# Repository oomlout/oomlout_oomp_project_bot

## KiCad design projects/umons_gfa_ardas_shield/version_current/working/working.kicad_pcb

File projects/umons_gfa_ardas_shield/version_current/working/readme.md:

# OOMP Project  
## ardas-shield  by UMONS-GFA  
  
oomp key: oomp_projects_flat_umons_gfa_ardas_shield  
(snippet of original readme)  

  full source readme at [readme_src.md](readme_src.md)  
  
source repo at: [https://github.com/UMONS-GFA/ardas-shield](https://github.com/UMONS-GFA/ardas-shield)  
## Board  

## Schematic  

[schematic pdf](working_schematic.pdf)  
## Images

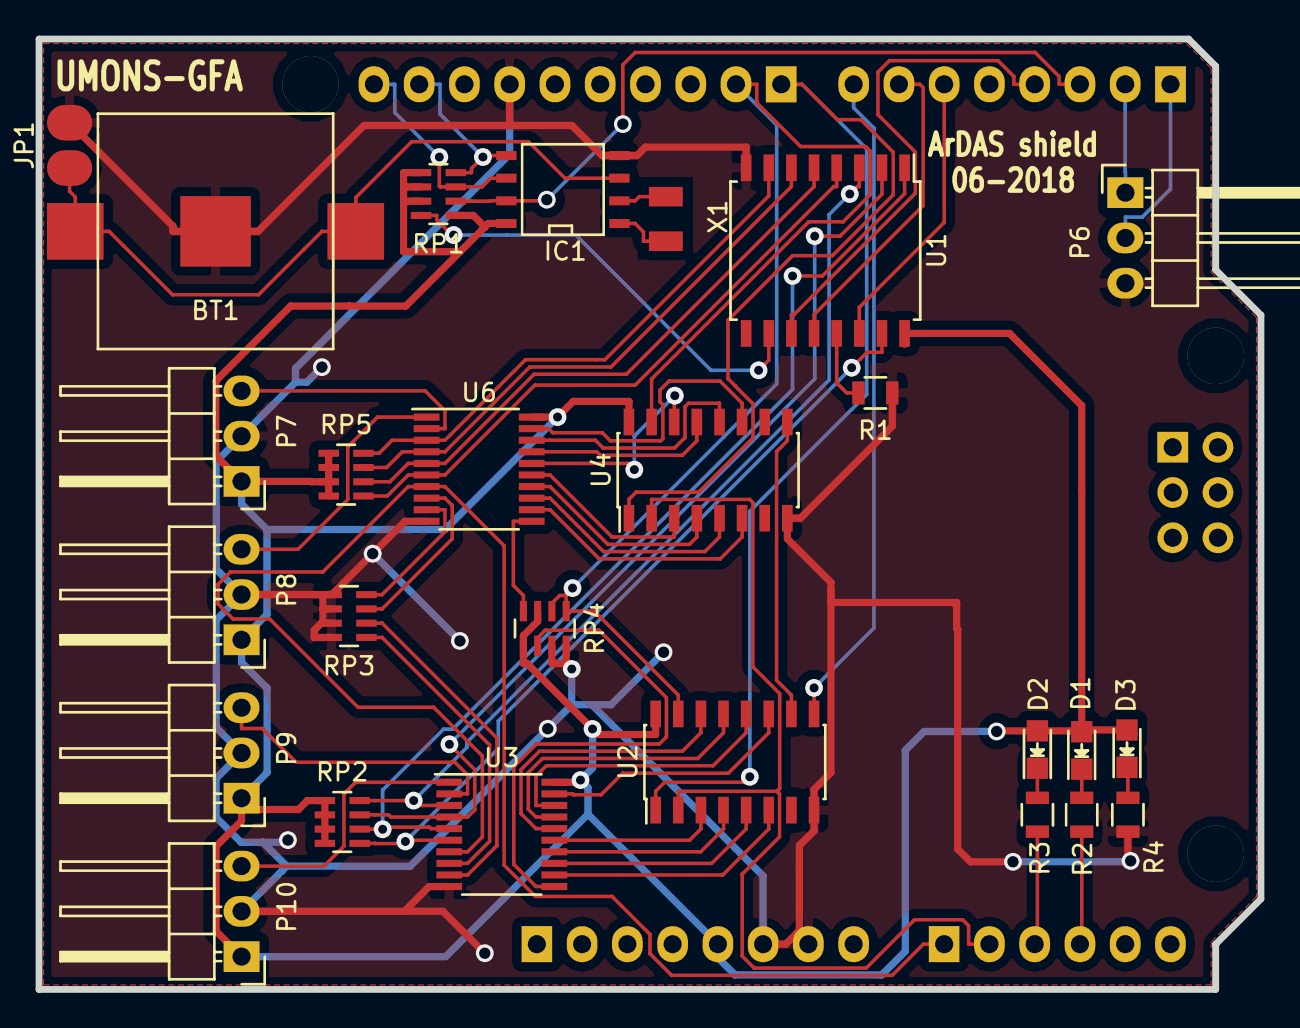
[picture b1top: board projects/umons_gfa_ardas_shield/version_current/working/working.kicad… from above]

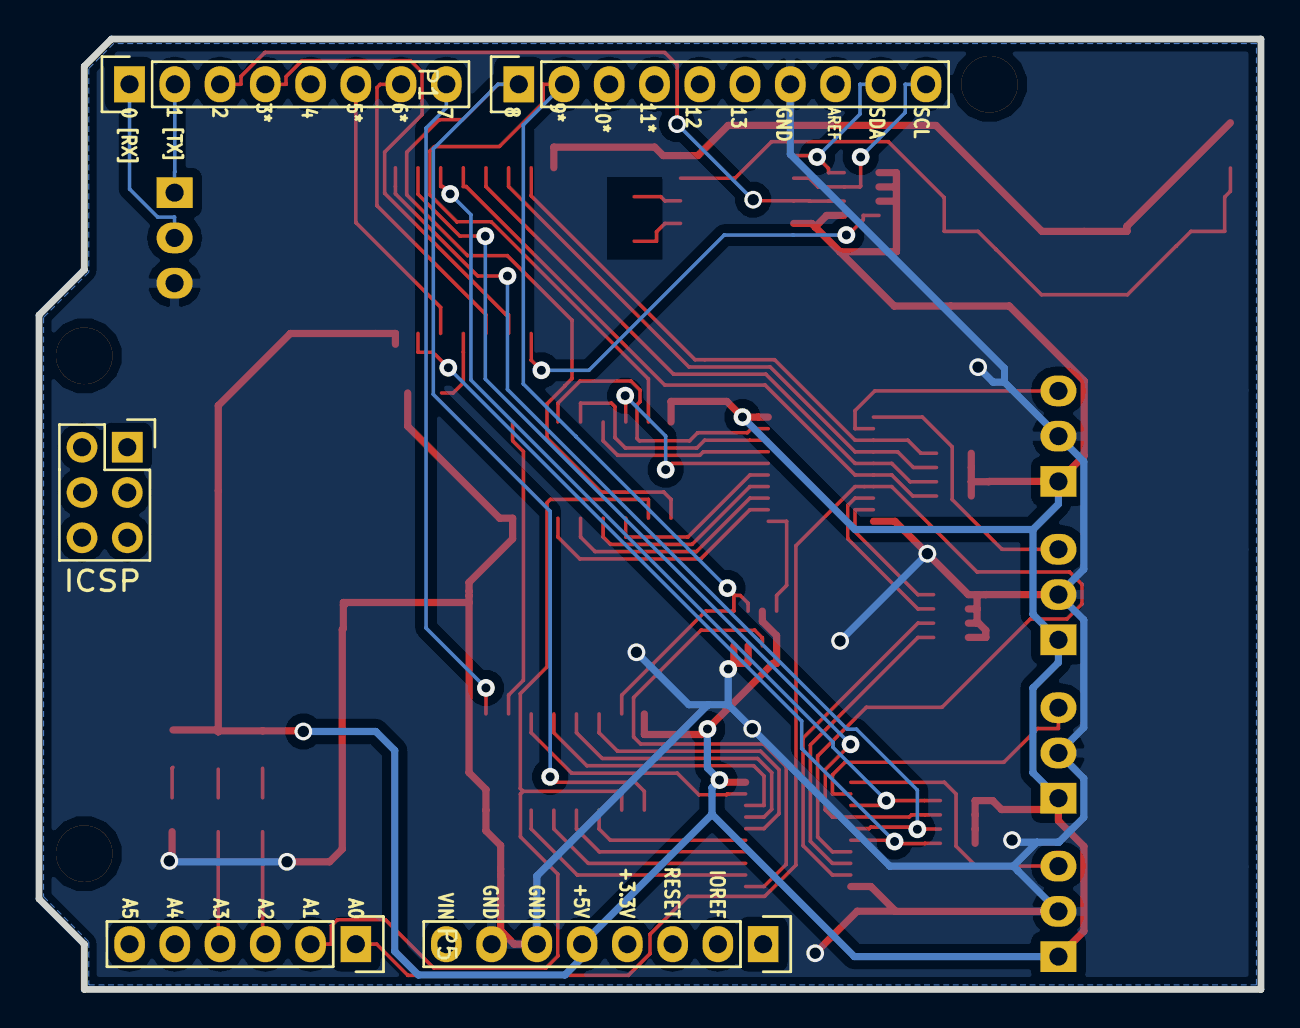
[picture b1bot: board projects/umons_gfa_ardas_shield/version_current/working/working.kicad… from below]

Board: 2 copper layers, 68.6 x 53.3 mm, 34 parts (5 on the bottom side), 60 nets.

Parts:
BT1: Battery; BATTERY_KEYSTONE_12mm
D1: LED; LED-0805
D2: LED Yellow; LED-0805
D3: LED Red; LED-0805
IC1: DS1307; SOIC-8-N
JP1: Jumper_NO_Small; small_no_jumper
P1: CONN_10; Pin_Header_Straight_1x10
P2, P3: CONN_8; Pin_Header_Straight_1x08
P4: CONN_ICSP; Socket_Strip_Straight_2x03
P5: CONN_6; Pin_Header_Straight_1x06
P6: TTL_COMM; Pin_Header_Angled_1x03
P7, P8, P9, P10: CONN_01X03; Pin_Header_Angled_1x03
R1: 10k; R_0805
R2, R3: 150 Ohm; R_0805
R4: 160 Ohm; R_0805
RP1: R_4x4.7k; R_Array_Convex_4x0603
RP2, RP3, RP4, RP5: R_4x10k; R_Array_Convex_4x0603
U1: 74HC595; SOIC-16_7.5x10.3mm_Pitch1.27mm
U2, U4: 74HC165; SOIC-16_3.9x9.9mm_Pitch1.27mm
U3, U6: SN74LV8154; TSSOP-20_4.4x6.5mm_Pitch0.65mm
V4, V5, V6: MountingHole_125mil
X1: CRYSTAL; XTAL_ABRACON_ABS07

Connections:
+5V: D1.2, D2.2, D3.2, IC1.8, P2.5, P7.1, P8.1, P9.1, P10.1, RP1.1, RP1.5, RP1.6, RP1.7, RP2.1, RP2.2, RP2.3, RP2.4, RP4.3, RP4.5, RP5.1, RP5.2, RP5.3, RP5.4, U1.16, U2.16, U3.20, U4.16, U6.20
A04: IC1.5, P1.9, RP1.4
A05: IC1.6, P1.10, RP1.3
CH1: P10.3, U3.1
CH2: P9.3, U3.2
CH3: P8.3, U6.1
CH4: P7.3, U6.2
D00: P3.1, P6.2
D01: P3.2, P6.1
D02: IC1.7, P3.3, RP1.2
D03: P3.4, U1.11
D05: P3.6, U1.14
D06: P3.7, U1.12
D07: P3.8, U2.9
D08: P1.1, U2.1, U4.1
D09: P1.2, RP4.1, RP4.2, U2.15, U4.15
D14: P5.1, U3.7, U6.7
D15: P5.2, U2.2, U4.2
D16: P5.3, R3.2
D17: P5.4, R2.2
GND: BT1.2, IC1.4, JP1.1, P1.7, P2.6, P2.7, P6.3, P7.2, P8.2, P9.2, P10.2, R1.1, R4.2, RP3.5, RP3.6, RP3.7, RP3.8, RP4.7, RP4.8, U1.8, U2.8, U3.10, U4.8, U6.10
unnamed: BT1.1, IC1.3, JP1.2
unnamed: D1.1, R2.1
unnamed: D2.1, R3.1
unnamed: D3.1, R4.1
unnamed: IC1.1, X1.1
unnamed: IC1.2, X1.2
unnamed: R1.2, U1.13
unnamed: RP1.8, U1.10
unnamed: RP2.5, U1.15, U3.6
unnamed: RP2.6, U1.1, U3.5
unnamed: RP2.7, U1.2, U3.4
unnamed: RP2.8, U1.3, U3.3
unnamed: RP3.1, U3.8
unnamed: RP3.2, U3.9
unnamed: RP3.3, U6.8
unnamed: RP3.4, U6.9
unnamed: RP4.4, U6.11
unnamed: RP4.6, U3.11
unnamed: RP5.5, U1.4, U6.6
unnamed: RP5.6, U1.5, U6.5
unnamed: RP5.7, U1.6, U6.4
unnamed: RP5.8, U1.7, U6.3
unnamed: U2.3, U3.15
unnamed: U2.4, U3.14
unnamed: U2.5, U3.13
unnamed: U2.6, U3.12
unnamed: U2.10, U4.9
unnamed: U2.11, U3.19
unnamed: U2.12, U3.18
unnamed: U2.13, U3.17
unnamed: U2.14, U3.16
unnamed: U4.3, U6.15
unnamed: U4.4, U6.14
unnamed: U4.5, U6.13
unnamed: U4.6, U6.12
unnamed: U4.11, U6.19
unnamed: U4.12, U6.18
unnamed: U4.13, U6.17
unnamed: U4.14, U6.16

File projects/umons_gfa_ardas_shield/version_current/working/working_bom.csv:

"Id";"Designator";"Footprint";"Quantity";"Designation";"Supplier and ref";
1;"V6,V4,V5";"MountingHole_125mil";3;"";;;
2;"BT1";"BATTERY_KEYSTONE_12mm";1;"Battery";;;
3;"IC1";"SOIC-8-N";1;"DS1307";;;
4;"JP1";"small_no_jumper";1;"Jumper_NO_Small";;;
5;"P1";"Pin_Header_Straight_1x10";1;"CONN_10";;;
6;"P2,P3";"Pin_Header_Straight_1x08";2;"CONN_8";;;
7;"P4";"Socket_Strip_Straight_2x03";1;"CONN_ICSP";;;
8;"P5";"Pin_Header_Straight_1x06";1;"CONN_6";;;
9;"P6";"Pin_Header_Angled_1x03";1;"TTL_COMM";;;
10;"P7,P8,P9,P10";"Pin_Header_Angled_1x03";4;"CONN_01X03";;;
11;"R1";"R_0805";1;"10k";;;
12;"R2,R3";"R_0805";2;"150 Ohm";;;
13;"R4";"R_0805";1;"160 Ohm";;;
14;"U1";"SOIC-16_7.5x10.3mm_Pitch1.27mm";1;"74HC595";;;
15;"U2,U4";"SOIC-16_3.9x9.9mm_Pitch1.27mm";2;"74HC165";;;
16;"X1";"XTAL_ABRACON_ABS07";1;"CRYSTAL";;;
17;"U6,U3";"TSSOP-20_4.4x6.5mm_Pitch0.65mm";2;"SN74LV8154";;;
18;"RP1";"R_Array_Convex_4x0603";1;"R_4x4.7k";;;
19;"RP2,RP3,RP4,RP5";"R_Array_Convex_4x0603";4;"R_4x10k";;;
20;"D2";"LED-0805";1;"LED Yellow";;;
21;"D3";"LED-0805";1;"LED Red";;;
22;"D1";"LED-0805";1;"LED Green";;;

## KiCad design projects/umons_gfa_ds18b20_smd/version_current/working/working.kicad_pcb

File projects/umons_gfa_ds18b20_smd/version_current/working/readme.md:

# OOMP Project  
## ds18b20-smd  by UMONS-GFA  
  
oomp key: oomp_projects_flat_umons_gfa_ds18b20_smd  
(snippet of original readme)  

  full source readme at [readme_src.md](readme_src.md)  
  
source repo at: [https://github.com/UMONS-GFA/ds18b20-smd](https://github.com/UMONS-GFA/ds18b20-smd)  
## Board  

## Schematic  

[schematic pdf](working_schematic.pdf)  
## Images

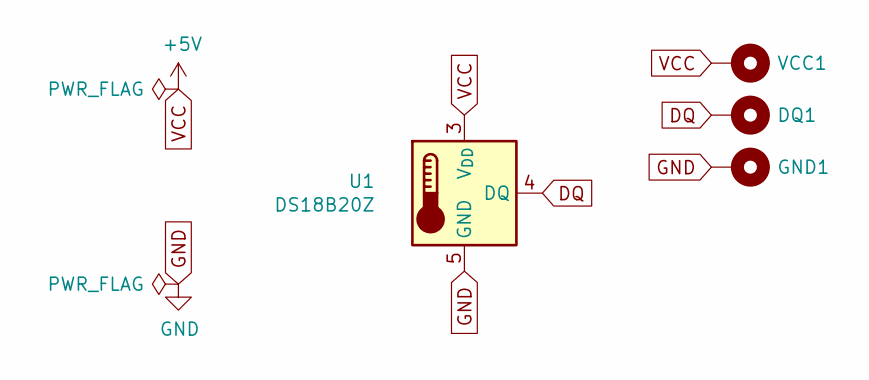
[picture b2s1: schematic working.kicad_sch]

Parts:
DQ1: Pad; PAD3mmx5mm
GND1: Pad; PAD3mmx5mm
U1: DS18B20Z; SOIC-8-N
VCC1: Pad; PAD3mmx5mm

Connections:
DQ: DQ1.1, U1.4 (DQ)
GND: GND1.1, U1.5 (GND)
VCC: U1.3 (V_{DD}), VCC1.1

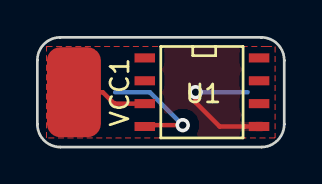
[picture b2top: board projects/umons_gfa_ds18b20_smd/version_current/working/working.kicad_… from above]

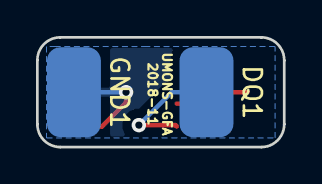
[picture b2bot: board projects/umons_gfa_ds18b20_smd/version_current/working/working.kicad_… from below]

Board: 2 copper layers, 13.7 x 6.1 mm, 4 parts (2 on the bottom side), 3 nets.

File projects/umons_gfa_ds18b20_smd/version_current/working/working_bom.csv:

"Id";"Designator";"Footprint";"Quantity";"Designation";"Supplier and ref";
1;"U1";"SOIC-8-N";1;"DS18B20Z";;;
2;"DQ1,GND1,VCC1";"PAD3mmx5mm";3;"Pad";;;

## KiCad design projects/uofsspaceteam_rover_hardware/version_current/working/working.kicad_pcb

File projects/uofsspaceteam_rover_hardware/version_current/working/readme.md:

# rover-hardware by UofSSpaceTeam  
This is a harvested standardized copy of a project from github.  
The original project can be found at:  
https://github.com/UofSSpaceTeam/rover-hardware  
Please consult that link for additional, details, files, and license information.  
Note: It was auto harvested and if the original repo had more than one board file or anything out of the ordinary the files here are likely not representative.

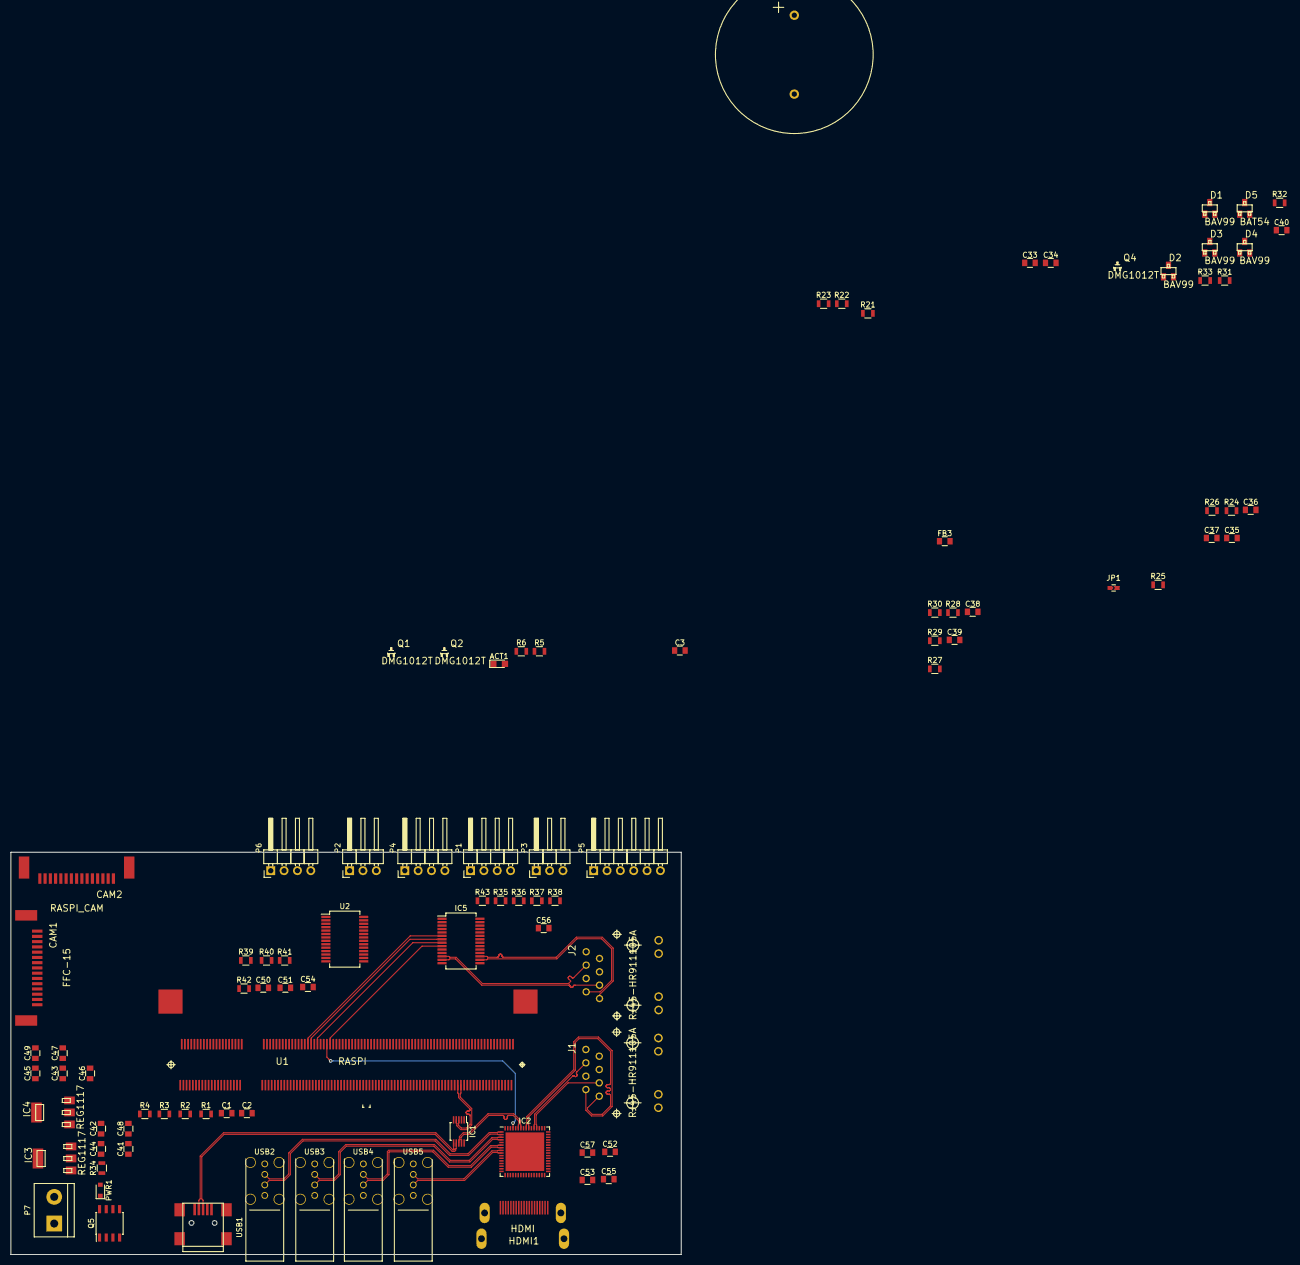
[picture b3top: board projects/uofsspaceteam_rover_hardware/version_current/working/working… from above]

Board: 4 copper layers, 127.5 x 76.5 mm, 141 parts (0 on the bottom side), 114 nets.

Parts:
ACT1: LED_0805
C1, C3, C21, C22, C26, C27, C30, C34, C41, C42, C45, C46, C47, C48, C49, C50: 10u; C_0805
C2, C5, C6, C7, C8: 20p; C_0805
C4, C9, C10, C11, C12, C13, C14, C15, C16, C17, C18, C19, C23, C24, C25, C28, C29, C31, C32, C33, C38, C39, C40, C53, C54, C55, C56, C57: 100n; C_0805
C20: 1u; C_0805
C35, C36, C37: 0.1u; C_0805
C43, C44: C_0805
C51, C52: 0.01u; C_0805
CAM1: FFC-15; FFC-15-PICAM
CAM2: RASPI_CAM; FFC-15-PICAM
D1, D2, D3, D4: BAV99; DIODE_SOT23
D5: BAT54; DIODE_SOT23
FB1, FB2: FERRITE_BEAD; C_0805
FB3: 80mA Ferrite; C_0805
HDMI1: HDMI; RASPI_HDMI
IC1: FSUSB42MSOP10; MSOP-10_3x3mm_Pitch0.5mm
IC2: RASPI_LAN9514; QFN-64-1EP_9x9mm_Pitch0.5mm
IC3, IC4: REG1117; BURR-BROWN_SOT223
IC5: ENC28J60; SSOP-28_5.3x10.2mm_Pitch0.65mm
J1, J2: RJ45-HR911105A; HANRUN_RJ45
JP1: Jumper_NC_Small; J_0603
P1: CONN_I2C; Pin_Header_Angled_1x04_Pitch2.54mm
P2: SERVO_PWM0; Pin_Header_Angled_1x03_Pitch2.54mm
P3: SERVO_PWM1; Pin_Header_Angled_1x03_Pitch2.54mm
P4: CONN_UART0; Pin_Header_Angled_1x04_Pitch2.54mm
P5: CONN_UART1_3DR; Pin_Header_Angled_1x06_Pitch2.54mm
P6: CAN_CONN_01X04; Pin_Header_Angled_1x04_Pitch2.54mm
P7: 5V POWER CONN; bornier2
PWR1: D_0805
Q1, Q2, Q3, Q4: DMG1012T; TRANSISTOR-FET_SC75_INFINEON
Q5: FDS6681Z; SOIC-8_3.9x4.9mm_Pitch1.27mm
R1, R2, R3, R26, R33: 100k; R_0805
R4, R5, R9, R10: 47k; R_0805
R6, R22, R23, R27, R28, R29, R30, R31, R32, R34: 1k8; R_0805
R7, R8, R25, R42, R43: 1k; R_0805
R11: 10; R_0805
R12, R13, R14, R15: 49.9; R_0805
R16: 12k4; R_0805
R17, R18, R19, R20: 12k; R_0805
R21: 400; R_0805
R24: 100; R_0805
R35, R36: 10k; R_0805
R37, R38, R40, R41: 50; R_0805
R39: 2.32k; R_0805
SP1: SPEAKER; AI-3035-TWT
U1: RASPI; RASPI_SO-DIMM
U2: MCP25625; SSOP-28_5.3x10.2mm_Pitch0.65mm
USB1: USB-TYPA; MINI-B-USBR
USB2, USB3, USB4, USB5: USB2; USB-A-UPRIGHT

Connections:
+1V8: C43.1, C45.1, C47.1, IC3.2, R5.1, R33.1, U1.183, U1.184, U1.185, U1.186
+3V3: C1.1, C3.1, C4.1, C10.1, C12.1, C23.1, C24.1, C25.1, C31.2, C32.2, C33.2, C35.1, C37.1, C38.2, C39.2, C44.1, C46.1, C48.1, C49.1, C53.1, C54.1, C55.1, C56.1, C57.1, CAM1.15, CAM2.15, FB2.2, FB3.1, IC1.1, IC2.11, IC2.19, IC2.27, IC2.33, IC2.39, IC2.40, IC2.46, IC4.2, IC5.15, IC5.19, IC5.20, IC5.25, IC5.28, P1.1, P4.1, R6.1, R7.1, R8.1, R9.1, R11.2, R12.1, R13.2, R14.2, R15.2, R18.1, R19.2, R20.1, R22.1, R23.2, R26.1, R27.1, R28.1, R29.1, R30.1, R34.1, R35.1, R36.1, U1.39, U1.40, U1.41, U1.42, U1.189, U1.190, U1.191, U1.192, U1.193, U1.194, U2.1, U2.19
+5V: C21.1, C22.1, C26.1, C27.1, C34.2, C36.1, C41.1, C42.1, D5.2, IC3.3, IC4.3, P2.2, P3.2, P5.3, P6.1, Q5.1, Q5.2, Q5.3, R31.1, R32.1, U1.197, U1.198, U1.199, U1.200, U2.27, USB2.VBUS, USB3.VBUS, USB4.VBUS, USB5.VBUS
/CAM0_C_N: CAM1.8, U1.144
/CAM0_C_P: CAM1.9, U1.142
/CAM0_D0_N: CAM1.2, U1.138
/CAM0_D0_P: CAM1.3, U1.136
/CAM0_D1_N: CAM1.5, U1.150
/CAM0_D1_P: CAM1.6, U1.148
/CAM1_C_N: CAM2.8, U1.149
/CAM1_C_P: CAM2.9, U1.147
/CAM1_D0_N: CAM2.2, U1.161
/CAM1_D0_P: CAM2.3, U1.159
/CAM1_D1_N: CAM2.5, U1.155
/CAM1_D1_P: CAM2.6, U1.153
/GPIO0: CAM2.14, R28.2, U1.3
/GPIO1: CAM2.13, R30.2, U1.5
/GPIO5: CAM2.12, U1.17
/GPIO6: IC2.12, R19.1, U1.21
/GPIO8: U1.27, U2.17
/GPIO9: U1.29, U2.16
/GPIO10: U1.33, U2.15
/GPIO11: U1.35, U2.14
/GPIO21: CAM2.11, U1.71
/GPIO25: U1.83, U2.13
/GPIO28: CAM1.14, R3.2, R27.2, U1.28
/GPIO29: CAM1.13, R1.2, R29.2, U1.30
/GPIO30: CAM1.11, U1.34
/GPIO31: CAM1.12, U1.36
/GPIO34: IC5.23, U1.52
/GPIO39: IC5.4, U1.66
/GPIO40: IC5.6, U1.70
/GPIO41: IC5.7, U1.72
/GPIO42: IC5.8, U1.76
/GPIO43: U1.78, U2.9
/GPIO44: IC2.61, R2.2, U1.82
/GPIO45: IC5.9, R35.2, U1.84
/HDMI_CEC: C2.1, D1.3, HDMI1.13, U1.171
/HDMI_CK_N: HDMI1.12, U1.111
/HDMI_CK_P: HDMI1.10, U1.113
/HDMI_D0_N: HDMI1.9, U1.117
/HDMI_D0_P: HDMI1.7, U1.119
/HDMI_D1_N: HDMI1.6, U1.123
/HDMI_D1_P: HDMI1.4, U1.125
/HDMI_D2_N: HDMI1.3, U1.129
/HDMI_D2_P: HDMI1.1, U1.131
/HDMI_SCL: D2.3, HDMI1.15, R32.2, U1.175
/HDMI_SDA: D3.3, HDMI1.16, R31.2, U1.173
/USBD_N: IC1.4, U1.167
/USBD_P: IC1.3, U1.165
/USSTCM CONN/SCL: P1.4, R23.1
/USSTCM CONN/SDA: P1.3, R22.2
/USSTCM LAN/ETH_RX_N: C8.1, IC2.53, J1.6, R12.2
/USSTCM LAN/ETH_RX_P: C7.1, IC2.52, J1.3, R13.1
/USSTCM LAN/ETH_TX_N: C6.1, IC2.56, J1.2, R14.1
/USSTCM LAN/ETH_TX_P: C5.1, IC2.55, J1.1, R15.1
/USSTCM LAN/NLNKA_LED: IC2.21, J1.10
/USSTCM LAN/NSPD_LED: IC2.22, J1.11
/USSTCM LAN/RCT: C9.1, J1.4, J1.5, R11.1
/USSTCM LAN/USB2_N: IC2.1, USB2.D-
/USSTCM LAN/USB2_P: IC2.2, USB2.D+
/USSTCM LAN/USB3_N: IC2.3, USB3.D-
/USSTCM LAN/USB3_P: IC2.4, USB3.D+
/USSTCM LAN/USB4_N: IC2.6, USB4.D-
/USSTCM LAN/USB4_P: IC2.7, USB4.D+
/USSTCM LAN/USB5_N: IC2.8, USB5.D-
/USSTCM LAN/USB5_P: IC2.9, USB5.D+
/USSTCM LAN/USB_BOOT_N: IC1.6, USB1.D-
/USSTCM LAN/USB_BOOT_P: IC1.7, USB1.D+
/USSTCM LAN/USB_LAN_N: IC1.8, IC2.58
/USSTCM LAN/USB_LAN_P: IC1.9, IC2.59
/USSTCM LAN/VDD18CORE: C28.2, C29.2, C30.2, IC2.15, IC2.38
/USSTCM LAN/VDD18PLL: C15.2, FB1.1, IC2.48
/USSTCM_CAN_LITE/CAN_N: P6.3, R24.2, U2.4
/USSTCM_CAN_LITE/CAN_P: JP1.2, P6.4, U2.3
/USSTCM_LAN2/LNKA_LED: IC5.27, J2.9
/USSTCM_LAN2/RCT: C51.1, J2.5, R37.2, R38.1
/USSTCM_LAN2/RD+: IC5.13, J2.3, R37.1
/USSTCM_LAN2/RD-: IC5.12, J2.6, R38.2
/USSTCM_LAN2/SPD_LED: IC5.26, J2.12
/USSTCM_LAN2/TCT: C52.1, FB3.2, J2.4, R40.2, R41.1
/USSTCM_LAN2/TD+: IC5.17, J2.1, R40.1
/USSTCM_LAN2/TD-: IC5.16, J2.2, R41.2
/USSTCM_VIDEO/5V_HDMI: C40.1, D1.2, D2.2, D3.2, D4.2, D5.1, HDMI1.18
/USSTCM_VIDEO/GPIO46: Q4.3, R33.2
/VUSB_BOOT: Q1.1, Q3.1, R4.1, R10.1, USB1.VBUS
GND: C1.2, C2.2, C3.2, C4.2, C5.2, C6.2, C7.2, C8.2, C9.2, C10.2, C11.1, C12.2, C13.1, C14.1, C15.1, C16.1, C17.1, C18.1, C19.1, C20.1, C21.2, C22.2, C23.2, C24.2, C25.2, C26.2, C27.2, C28.1, C29.1, C30.1, C31.1, C32.1, C33.1, C34.1, C35.2, C36.2, C37.2, C38.1, C39.1, C40.2, C41.2, C42.2, C43.2, C44.2, C45.2, C46.2, C47.2, C48.2, C49.2, C50.2, C51.2, C52.2, C53.2, C54.2, C55.2, C56.2, C57.2, CAM1.1, CAM1.4, CAM1.7, CAM1.10, CAM1.16, CAM1.17, CAM2.1, CAM2.4, CAM2.7, CAM2.10, CAM2.16, CAM2.17, D1.1, D2.1, D3.1, D4.1, HDMI1.2, HDMI1.5, HDMI1.8, HDMI1.11, HDMI1.17, HDMI1.P$1, HDMI1.P$2, HDMI1.P$3, HDMI1.P$4, IC1.5, IC1.10, IC2.34, IC2.44, IC2.65, IC3.1, IC4.1, IC5.2, IC5.11, IC5.18, IC5.21, IC5.22, J1.8, J2.8, P1.2, P2.1, P3.1, P4.2, P5.1, P6.2, P7.2, PWR1.1, Q2.2, Q3.2, Q4.2, Q5.4, R1.1, R2.1, R3.1, R4.2, R10.2, R16.1, R17.2, R25.2, R39.2, R42.1, R43.1, SP1.2, U1.1, U1.7, U1.13, U1.19, U1.25, U1.26, U1.31, U1.32, U1.37, U1.38, U1.43, U1.44, U1.49, U1.50, U1.55, U1.56, U1.61, U1.62, U1.67, U1.68, U1.73, U1.74, U1.79, U1.80, U1.85, U1.86, U1.91, U1.92, U1.97, U1.98, U1.103, U1.104, U1.109, U1.110, U1.115, U1.116, U1.121, U1.122, U1.127, U1.133, U1.134, U1.139, U1.140, U1.145, U1.146, U1.151, U1.152, U1.157, U1.163, U1.164, U1.168, U1.169, U1.170, U1.181, U1.182, U1.187, U1.188, U1.195, U1.196, U1.G1, U1.G2, U2.26, USB1.GND, USB2.GND, USB3.GND, USB4.GND, USB5.GND
unnamed: ACT1.1, Q1.2, Q2.3
unnamed: ACT1.2, R6.2
unnamed: C11.2, C14.2, C16.2, C17.2, C18.2, C19.2, FB2.1, IC2.5, IC2.10, IC2.49, IC2.51, IC2.54, IC2.57, IC2.64
unnamed: C20.2, FB1.2, IC2.62
unnamed: C50.1, IC5.1
unnamed: D4.3, HDMI1.19, Q4.1
unnamed: IC1.2, Q3.3, R9.2
unnamed: IC2.28, R20.2
unnamed: IC2.41, R18.2
unnamed: IC2.50, R16.2
unnamed: IC2.63, R17.1
unnamed: IC5.10, R36.2
unnamed: IC5.14, R39.1
unnamed: J1.9, R8.2
unnamed: J1.12, R7.2
unnamed: J2.10, R43.2
unnamed: J2.11, R42.2
unnamed: JP1.1, R24.1
unnamed: P7.1, Q5.5, Q5.6, Q5.7, Q5.8
unnamed: PWR1.2, R34.2
unnamed: Q1.3, U1.2
unnamed: Q2.1, R5.2, U1.90
unnamed: R21.1, SP1.1
unnamed: R25.1, U2.5
unnamed: R26.2, U2.18
unnamed: U2.20, U2.24
unnamed: U2.21, U2.28

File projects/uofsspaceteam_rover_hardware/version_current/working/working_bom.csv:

"Id";"Designator";"Footprint";"Quantity";"Designation";"Supplier and ref";
1;"C1,C3,C21,C22,C26,C27,C30,C34,C41,C42,C45,C46,C47,C48,C49,C50";"C_0805";16;"10u";;;
2;"C2,C5,C6,C7,C8";"C_0805";5;"20p";;;
3;"C4,C9,C10,C11,C12,C13,C14,C15,C16,C17,C18,C19,C23,C24,C25,C28,C29,C31,C32,C33,C38,C39,C40,C53,C54,C55,C56,C57";"C_0805";28;"100n";;;
4;"C20";"C_0805";1;"1u";;;
5;"C35,C36,C37";"C_0805";3;"0.1u";;;
6;"C43,C44";"C_0805";2;"~";;;
7;"C51,C52";"C_0805";2;"0.01u";;;
8;"D1,D2,D3,D4";"DIODE_SOT23";4;"BAV99";;;
9;"D5";"DIODE_SOT23";1;"BAT54";;;
10;"FB1,FB2";"C_0805";2;"FERRITE_BEAD";;;
11;"HDMI1";"RASPI_HDMI";1;"HDMI";;;
12;"IC3,IC4";"BURR-BROWN_SOT223";2;"REG1117";;;
13;"IC5";"SSOP-28_5.3x10.2mm_Pitch0.65mm";1;"ENC28J60";;;
14;"JP1";"J_0603";1;"Jumper_NC_Small";;;
15;"P1";"Pin_Header_Angled_1x04_Pitch2.54mm";1;"CONN_I2C";;;
16;"P2";"Pin_Header_Angled_1x03_Pitch2.54mm";1;"SERVO_PWM0";;;
17;"P3";"Pin_Header_Angled_1x03_Pitch2.54mm";1;"SERVO_PWM1";;;
18;"P4";"Pin_Header_Angled_1x04_Pitch2.54mm";1;"CONN_UART0";;;
19;"P5";"Pin_Header_Angled_1x06_Pitch2.54mm";1;"CONN_UART1_3DR";;;
20;"P6";"Pin_Header_Angled_1x04_Pitch2.54mm";1;"CAN_CONN_01X04";;;
21;"P7";"bornier2";1;"5V POWER CONN";;;
22;"Q1,Q2,Q3,Q4";"TRANSISTOR-FET_SC75_INFINEON";4;"DMG1012T";;;
23;"Q5";"SOIC-8_3.9x4.9mm_Pitch1.27mm";1;"FDS6681Z";;;
24;"R1,R2,R3,R26,R33";"R_0805";5;"100k";;;
25;"R4,R5,R9,R10";"R_0805";4;"47k";;;
26;"R6,R22,R23,R27,R28,R29,R30,R31,R32,R34";"R_0805";10;"1k8";;;
27;"R7,R8,R25,R42,R43";"R_0805";5;"1k";;;
28;"R11";"R_0805";1;"10";;;
29;"R12,R13,R14,R15";"R_0805";4;"49.9";;;
30;"R16";"R_0805";1;"12k4";;;
31;"R17,R18,R19,R20";"R_0805";4;"12k";;;
32;"R21";"R_0805";1;"400";;;
33;"R24";"R_0805";1;"100";;;
34;"R35,R36";"R_0805";2;"10k";;;
35;"R37,R38,R40,R41";"R_0805";4;"50";;;
36;"R39";"R_0805";1;"2.32k";;;
37;"U1";"RASPI_SO-DIMM";1;"RASPI";;;
38;"U2";"SSOP-28_5.3x10.2mm_Pitch0.65mm";1;"MCP25625";;;
39;"CAM1";"FFC-15-PICAM";1;"FFC-15";;;
40;"CAM2";"FFC-15-PICAM";1;"RASPI_CAM";;;
41;"PWR1";"D_0805";1;"~";;;
42;"IC2";"QFN-64-1EP_9x9mm_Pitch0.5mm";1;"RASPI_LAN9514";;;
43;"USB2,USB3,USB4,USB5";"USB-A-UPRIGHT";4;"USB2";;;
44;"USB1";"MINI-B-USBR";1;"USB-TYPA";;;
45;"ACT1";"LED_0805";1;"~";;;
46;"IC1";"MSOP-10_3x3mm_Pitch0.5mm";1;"FSUSB42MSOP10";;;
47;"FB3";"C_0805";1;"80mA Ferrite";;;
48;"SP1";"AI-3035-TWT";1;"SPEAKER";;;

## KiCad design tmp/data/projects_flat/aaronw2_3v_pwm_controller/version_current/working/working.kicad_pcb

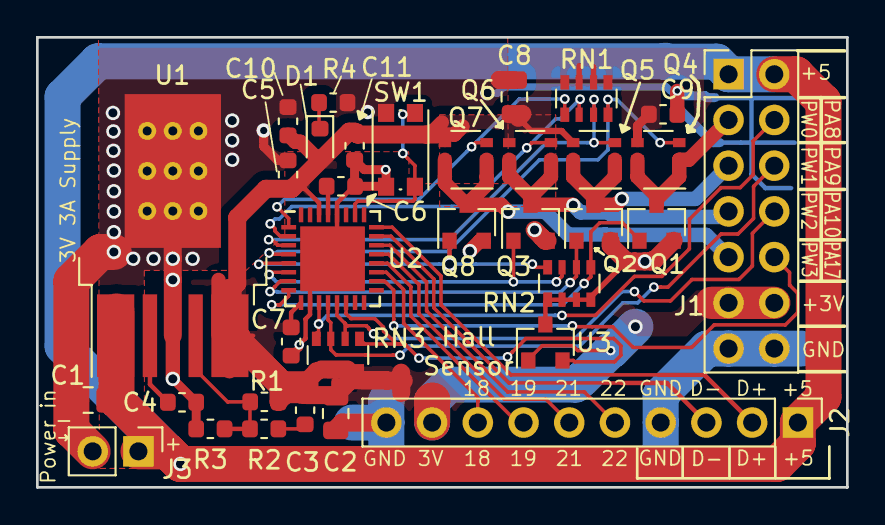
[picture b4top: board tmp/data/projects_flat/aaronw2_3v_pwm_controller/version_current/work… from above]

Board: 2 copper layers, 45.0 x 25.0 mm, 34 parts (0 on the bottom side), 32 nets.

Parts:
C1: 22uF; C_0805_2012Metric
C2, C8: 47uF; C_0805_2012Metric
C3: 91pF; C_0603_1608Metric
C4: 0.022uF; C_0603_1608Metric
C5, C6, C7, C10: 1uF; C_0603_1608Metric
C9, C11: 0.1uF; C_0603_1608Metric
D1: LED; LED_0603_1608Metric
J1: Conn_02x07_Odd_Even; PinHeader_2x07_P2.54mm_Vertical
J2: Conn_01x10; PinHeader_1x10_P2.54mm_Vertical
J3: Conn_01x02; PinHeader_1x02_P2.54mm_Vertical
Q1, Q2, Q3, Q8: DMN1019USN; SOT-23
Q4, Q5, Q6, Q7: SI3407DV-T1-GE3; TSOP-6_1.65x3.05mm_P0.95mm
R1: 82.5K; R_0603_1608Metric
R2: 1.27K; R_0603_1608Metric
R3: 30K; R_0603_1608Metric
R4: 330; R_0603_1608Metric
RN1, RN2: 100K; R_Array_Convex_4x0603
RN3: 10K; R_Array_Convex_4x0603
SW1: SW_SPST_KMR2
U1: LMZ10503; TO-PMOD-7_TabPin4
U2: ATSAMD21E18A-AF; QFN-32-1EP_5x5mm_P0.5mm_EP3.6x3.6mm
U3: DRV5032FCDBZT; SOT-23

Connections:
+3V3: C2.1, C3.1, C5.1, C7.1, C8.1, C9.1, C10.1, C11.1, D1.2, J1.11, J1.12, J2.9, Q4.4, Q5.4, Q6.4, Q7.4, R1.1, RN1.5, RN1.6, RN1.7, RN1.8, RN3.5, RN3.6, RN3.7, RN3.8, U1.6, U1.7, U2.9, U2.30, U3.1
+5V: C1.1, J1.1, J1.2, J2.1, J3.1, U1.1, U1.2
/D_N: J2.3, U2.23
/D_P: J2.2, U2.24
/PA00: Q7.3, RN1.1, U2.1
/PA01: Q6.3, RN1.2, U2.2
/PA02: Q5.3, RN1.3, U2.3
/PA03: Q4.3, RN1.4, U2.4
/PA04: Q8.1, RN2.8, U2.5
/PA05: Q3.1, RN2.7, U2.6
/PA06: Q2.1, RN2.6, U2.7
/PA07: Q1.1, RN2.5, U2.8
/PA08: J1.4, RN3.4, U2.11
/PA09: J1.6, RN3.3, U2.12
/PA10: J1.8, RN3.2, U2.13
/PA11: RN3.1, U2.14, U3.2
/PA17: J1.10, U2.18
/PA18: J2.8, U2.19
/PA19: J2.7, U2.20
/PA21: J2.6, U2.21
/PA22: J2.5, U2.22
/PWM0: J1.3, Q1.3, Q4.1, Q4.2, Q4.5, Q4.6
/PWM1: J1.5, Q2.3, Q5.1, Q5.2, Q5.5, Q5.6
/PWM2: J1.7, Q3.3, Q6.1, Q6.2, Q6.5, Q6.6
/PWM3: J1.9, Q7.1, Q7.2, Q7.5, Q7.6, Q8.3
GND: C1.2, C2.2, C4.2, C5.2, C6.2, C7.2, C8.2, C9.2, C10.2, C11.2, J1.13, J1.14, J2.4, J2.10, J3.2, Q1.2, Q2.2, Q3.2, Q8.2, R3.2, R4.1, RN2.1, RN2.2, RN2.3, RN2.4, SW1.1, U1.4, U2.10, U2.28, U2.33, U3.3
unnamed: C3.2, R2.1
unnamed: C4.1, U1.3
unnamed: C6.1, U2.29
unnamed: D1.1, R4.2
unnamed: R1.2, R2.2, R3.1, U1.5
unnamed: SW1.2, U2.26

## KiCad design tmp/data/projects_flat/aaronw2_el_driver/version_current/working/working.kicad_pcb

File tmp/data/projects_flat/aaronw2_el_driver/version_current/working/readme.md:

# el-driver by aaronw2  
This is a harvested standardized copy of a project from github.  
The original project can be found at:  
https://github.com/aaronw2/el-driver  
Please consult that link for additional, details, files, and license information.  
Note: It was auto harvested and if the original repo had more than one board file or anything out of the ordinary the files here are likely not representative.

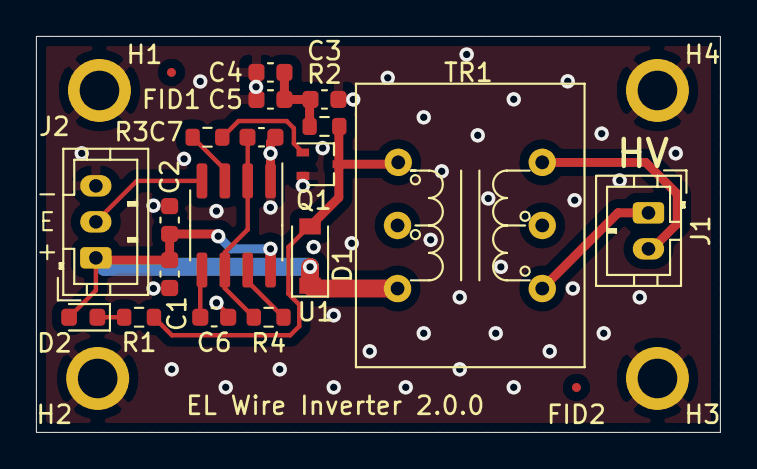
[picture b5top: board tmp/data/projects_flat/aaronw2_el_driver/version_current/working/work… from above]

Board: 2 copper layers, 38.0 x 22.0 mm, 24 parts (0 on the bottom side), 13 nets.

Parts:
C1: 10uF; C_0603_1608Metric
C2: 1uF; C_0603_1608Metric
C3: 4.7nF; C_0603_1608Metric
C4, C5: 1nF; C_0603_1608Metric
C6: 10nF; C_0603_1608Metric
C7: 47nF; C_0603_1608Metric
D1: SS24FL; D_SOD-123
D2: LED; LED_0603_1608Metric
FID1, FID2: FIDUCIAL_1MM; Fiducial_0.5mm_Mask1mm
H1, H2, H3, H4: MountingHole_Pad; MountingHole_2.2mm_M2_ISO7380_Pad
J1: Conn_01x02; JST_PH_B2B-PH-K_1x02_P2.00mm_Vertical
J2: Conn_01x03; JST_PH_B3B-PH-K_1x03_P2.00mm_Vertical
Q1: BSS214NW; SOT-323_SC-70
R1: 220; R_0603_1608Metric
R2: 39.2; R_0603_1608Metric
R3: 100k; R_0603_1608Metric
R4: 10k; R_0603_1608Metric
TR1: Transformer-EI14; Transformer_42XL_EI-14
U1: NE555D; SOIC-8_3.9x4.9mm_P1.27mm

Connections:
+5V: C1.1, C2.1, D1.1, D2.2, J2.1, TR1.3, U1.8
/EN: J2.2, U1.4
GND: C1.2, C2.2, C3.2, C4.2, C5.2, C6.2, C7.2, H1.1, H2.1, H3.1, H4.1, J2.3, Q1.2, U1.1
unnamed: C3.1, C4.1, C5.1, R2.2
unnamed: C6.1, U1.5
unnamed: C7.1, R4.2, U1.2, U1.6
unnamed: D1.2, Q1.3, R1.2, R2.1, TR1.1
unnamed: D2.1, R1.1
unnamed: J1.1, TR1.4
unnamed: J1.2, TR1.6
unnamed: Q1.1, R3.2
unnamed: R3.1, U1.3
unnamed: R4.1, U1.7

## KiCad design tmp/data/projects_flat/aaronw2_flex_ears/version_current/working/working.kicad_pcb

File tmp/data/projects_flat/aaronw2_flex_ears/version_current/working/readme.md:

# Flex-ears by aaronw2  
This is a harvested standardized copy of a project from github.  
The original project can be found at:  
https://github.com/aaronw2/Flex-ears  
Please consult that link for additional, details, files, and license information.  
Note: It was auto harvested and if the original repo had more than one board file or anything out of the ordinary the files here are likely not representative.

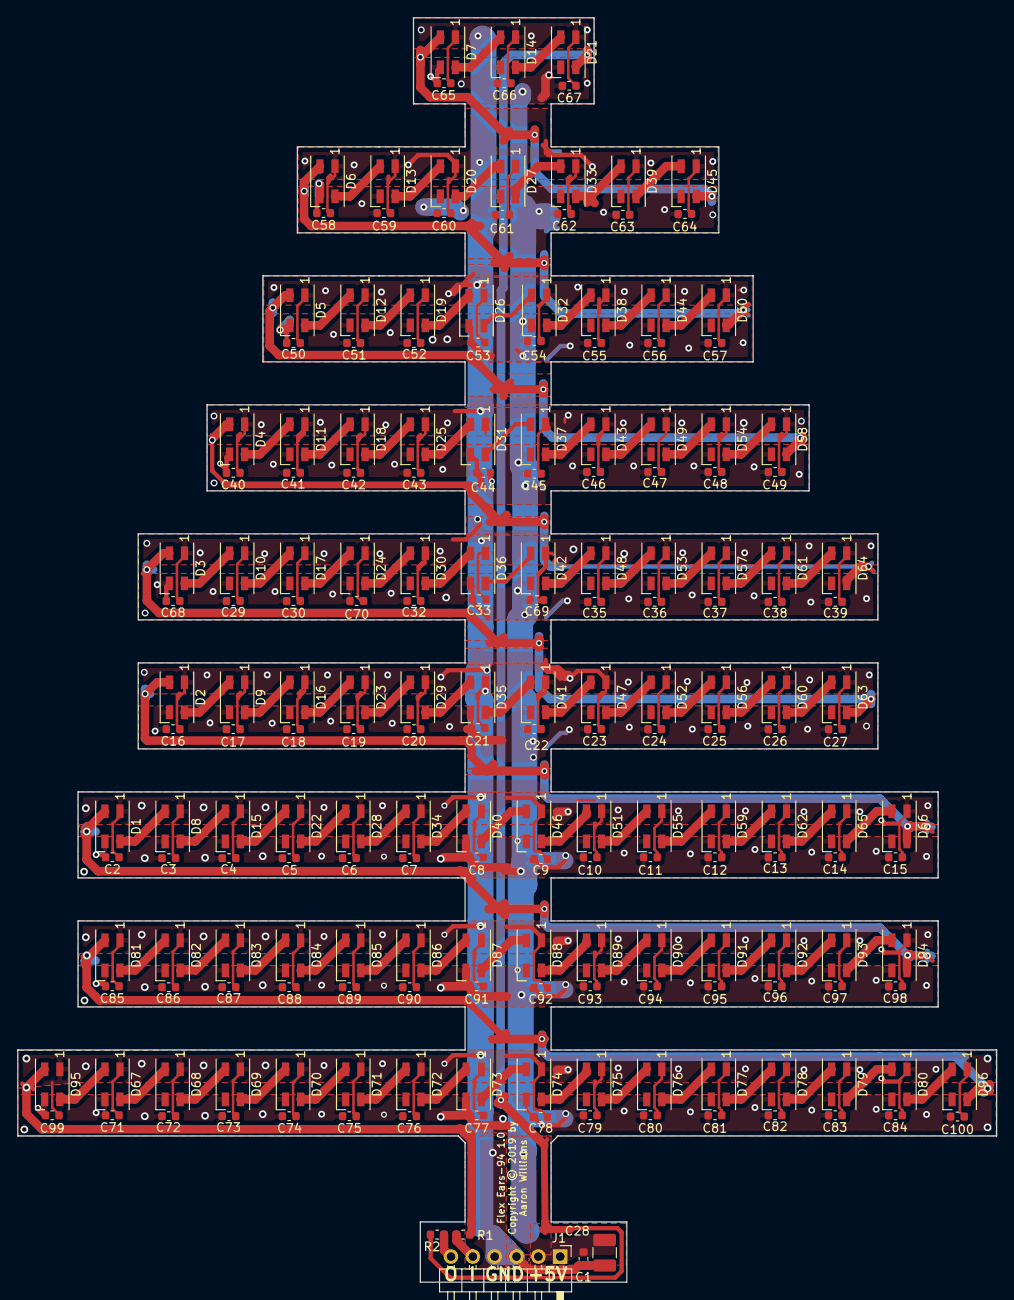
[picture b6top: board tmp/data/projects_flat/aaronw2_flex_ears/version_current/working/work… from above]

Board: 2 copper layers, 113.8 x 147.0 mm, 197 parts (0 on the bottom side), 101 nets.

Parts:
C1, C2, C3, C4, C5, C6, C7, C8, C9, C10, C11, C12, C13, C14, C15, C16, C17, C18, C19, C20, C21, C22, C23, C24, C26, C27, C29, C30, C32, C33, C35, C36, C37, C38, C39, C40, C41, C42, C43, C44, C45, C46, C47, C48, C49, C50, C51, C52, C53, C54, C55, C56, C57, C58, C59, C60, C61, C62, C63, C64, C65, C66, C67, C68, C69, C70, C71, C72, C73, C74, C75, C76, C77, C78, C79, C80, C81, C82, C83, C84, C85, C86, C87, C88, C89, C90, C91, C92, C93, C94, C95, C96, C97, C98, C99, C100: 1uF; C_0603_1608Metric
C25: 10uF; C_0603_1608Metric
C28: 100uF 10V; C_1210_3225Metric_Pad1.42x2.65mm_HandSolder
D1, D2, D3, D4, D5, D6, D7, D8, D9, D10, D11, D12, D13, D14, D15, D16, D17, D18, D19, D20, D21, D22, D23, D24, D25, D26, D27, D28, D29, D30, D31, D32, D33, D34, D35, D36, D37, D38, D39, D40, D41, D42, D43, D44, D45, D46, D47, D48, D49, D50, D51, D52, D53, D54, D55, D56, D57, D58, D59, D60, D61, D62, D63, D64, D65, D66, D67, D68, D69, D70, D71, D72, D73, D74, D75, D76, D77, D78, D79, D80, D81, D82, D83, D84, D85, D86, D87, D88, D89, D90, D91, D92, D93, D94, D95, D96: SK6812; LED_SK6812MINI_PLCC4_3.5x3.5mm_P1.75mm
J1: Conn_01x06_Male; Pin_Header_Angled_1x06_Pitch2.54mm
R1, R2: 22; R_0603_1608Metric

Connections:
/DI: D95.2, R1.1
/DIN: J1.5, R1.2
/DIN_1_2: D81.2, D96.4
/DIN_2_3: D1.2, D94.4
/DIN_3_4: D2.2, D66.4
/DIN_4_5: D3.2, D63.4
/DIN_5_6: D4.2, D64.4
/DIN_6_7: D5.2, D58.4
/DIN_7_8: D6.2, D50.4
/DIN_8_9: D7.2, D45.4
/DO: D21.4, R2.2
/DOUT: J1.6, R2.1
GND: C1.2, C2.2, C3.2, C4.2, C5.2, C6.2, C7.2, C8.2, C9.2, C10.2, C11.2, C12.2, C13.2, C14.2, C15.2, C16.2, C17.2, C18.2, C19.2, C20.2, C21.2, C22.2, C23.2, C24.2, C25.2, C26.2, C27.2, C28.2, C29.2, C30.2, C32.2, C33.2, C35.2, C36.2, C37.2, C38.2, C39.2, C40.2, C41.2, C42.2, C43.2, C44.2, C45.2, C46.2, C47.2, C48.2, C49.2, C50.2, C51.2, C52.2, C53.2, C54.2, C55.2, C56.2, C57.2, C58.2, C59.2, C60.2, C61.2, C62.2, C63.2, C64.2, C65.2, C66.2, C67.2, C68.2, C69.2, C70.2, C71.2, C72.2, C73.2, C74.2, C75.2, C76.2, C77.2, C78.2, C79.2, C80.2, C81.2, C82.2, C83.2, C84.2, C85.2, C86.2, C87.2, C88.2, C89.2, C90.2, C91.2, C92.2, C93.2, C94.2, C95.2, C96.2, C97.2, C98.2, C99.2, C100.2, D1.1, D2.1, D3.1, D4.1, D5.1, D6.1, D7.1, D8.1, D9.1, D10.1, D11.1, D12.1, D13.1, D14.1, D15.1, D16.1, D17.1, D18.1, D19.1, D20.1, D21.1, D22.1, D23.1, D24.1, D25.1, D26.1, D27.1, D28.1, D29.1, D30.1, D31.1, D32.1, D33.1, D34.1, D35.1, D36.1, D37.1, D38.1, D39.1, D40.1, D41.1, D42.1, D43.1, D44.1, D45.1, D46.1, D47.1, D48.1, D49.1, D50.1, D51.1, D52.1, D53.1, D54.1, D55.1, D56.1, D57.1, D58.1, D59.1, D60.1, D61.1, D62.1, D63.1, D64.1, D65.1, D66.1, D67.1, D68.1, D69.1, D70.1, D71.1, D72.1, D73.1, D74.1, D75.1, D76.1, D77.1, D78.1, D79.1, D80.1, D81.1, D82.1, D83.1, D84.1, D85.1, D86.1, D87.1, D88.1, D89.1, D90.1, D91.1, D92.1, D93.1, D94.1, D95.1, D96.1, J1.3, J1.4
unnamed: D1.4, D8.2
unnamed: D2.4, D9.2
unnamed: D3.4, D10.2
unnamed: D10.4, D17.2
unnamed: D4.4, D11.2
unnamed: D11.4, D18.2
unnamed: D5.4, D12.2
unnamed: D12.4, D19.2
unnamed: D6.4, D13.2
unnamed: D13.4, D20.2
unnamed: D7.4, D14.2
unnamed: D14.4, D21.2
unnamed: D8.4, D15.2
unnamed: D15.4, D22.2
unnamed: D9.4, D16.2
unnamed: D16.4, D23.2
unnamed: D17.4, D24.2
unnamed: D18.4, D25.2
unnamed: D19.4, D26.2
unnamed: D20.4, D27.2
unnamed: D22.4, D28.2
unnamed: D23.4, D29.2
unnamed: D24.4, D30.2
unnamed: D25.4, D31.2
unnamed: D26.4, D32.2
unnamed: D27.4, D33.2
unnamed: D28.4, D34.2
unnamed: D29.4, D35.2
unnamed: D30.4, D36.2
unnamed: D31.4, D37.2
unnamed: D32.4, D38.2
unnamed: D33.4, D39.2
unnamed: D34.4, D40.2
unnamed: D35.4, D41.2
unnamed: D36.4, D42.2
unnamed: D37.4, D43.2
unnamed: D38.4, D44.2
unnamed: D39.4, D45.2
unnamed: D40.4, D46.2
unnamed: D41.4, D47.2
unnamed: D42.4, D48.2
unnamed: D43.4, D49.2
unnamed: D44.4, D50.2
unnamed: D46.4, D51.2
unnamed: D47.4, D52.2
unnamed: D48.4, D53.2
unnamed: D49.4, D54.2
unnamed: D51.4, D55.2
unnamed: D52.4, D56.2
unnamed: D53.4, D57.2
unnamed: D54.4, D58.2
unnamed: D55.4, D59.2
unnamed: D56.4, D60.2
unnamed: D57.4, D61.2
unnamed: D59.4, D62.2
unnamed: D60.4, D63.2
unnamed: D61.4, D64.2
unnamed: D62.4, D65.2
unnamed: D65.4, D66.2
unnamed: D67.2, D95.4
unnamed: D67.4, D68.2
unnamed: D68.4, D69.2
unnamed: D69.4, D70.2
unnamed: D70.4, D71.2
unnamed: D71.4, D72.2
unnamed: D72.4, D73.2
unnamed: D73.4, D74.2
unnamed: D74.4, D75.2
unnamed: D75.4, D76.2
unnamed: D76.4, D77.2
unnamed: D77.4, D78.2
unnamed: D78.4, D79.2
unnamed: D79.4, D80.2
unnamed: D80.4, D96.2
unnamed: D81.4, D82.2
unnamed: D82.4, D83.2
unnamed: D83.4, D84.2
unnamed: D84.4, D85.2
unnamed: D85.4, D86.2
unnamed: D86.4, D87.2
unnamed: D87.4, D88.2
unnamed: D88.4, D89.2
unnamed: D89.4, D90.2
unnamed: D90.4, D91.2
unnamed: D91.4, D92.2
unnamed: D92.4, D93.2
unnamed: D93.4, D94.2
VCC: C1.1, C2.1, C3.1, C4.1, C5.1, C6.1, C7.1, C8.1, C9.1, C10.1, C11.1, C12.1, C13.1, C14.1, C15.1, C16.1, C17.1, C18.1, C19.1, C20.1, C21.1, C22.1, C23.1, C24.1, C25.1, C26.1, C27.1, C28.1, C29.1, C30.1, C32.1, C33.1, C35.1, C36.1, C37.1, C38.1, C39.1, C40.1, C41.1, C42.1, C43.1, C44.1, C45.1, C46.1, C47.1, C48.1, C49.1, C50.1, C51.1, C52.1, C53.1, C54.1, C55.1, C56.1, C57.1, C58.1, C59.1, C60.1, C61.1, C62.1, C63.1, C64.1, C65.1, C66.1, C67.1, C68.1, C69.1, C70.1, C71.1, C72.1, C73.1, C74.1, C75.1, C76.1, C77.1, C78.1, C79.1, C80.1, C81.1, C82.1, C83.1, C84.1, C85.1, C86.1, C87.1, C88.1, C89.1, C90.1, C91.1, C92.1, C93.1, C94.1, C95.1, C96.1, C97.1, C98.1, C99.1, C100.1, D1.3, D2.3, D3.3, D4.3, D5.3, D6.3, D7.3, D8.3, D9.3, D10.3, D11.3, D12.3, D13.3, D14.3, D15.3, D16.3, D17.3, D18.3, D19.3, D20.3, D21.3, D22.3, D23.3, D24.3, D25.3, D26.3, D27.3, D28.3, D29.3, D30.3, D31.3, D32.3, D33.3, D34.3, D35.3, D36.3, D37.3, D38.3, D39.3, D40.3, D41.3, D42.3, D43.3, D44.3, D45.3, D46.3, D47.3, D48.3, D49.3, D50.3, D51.3, D52.3, D53.3, D54.3, D55.3, D56.3, D57.3, D58.3, D59.3, D60.3, D61.3, D62.3, D63.3, D64.3, D65.3, D66.3, D67.3, D68.3, D69.3, D70.3, D71.3, D72.3, D73.3, D74.3, D75.3, D76.3, D77.3, D78.3, D79.3, D80.3, D81.3, D82.3, D83.3, D84.3, D85.3, D86.3, D87.3, D88.3, D89.3, D90.3, D91.3, D92.3, D93.3, D94.3, D95.3, D96.3, J1.1, J1.2

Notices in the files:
tmp/data/projects_flat/aaronw2_3v_pwm_controller/version_current/working/working.kicad_pcb:
Copyright © 2018-2019 by Aaron Williams
Copyright © 2019 by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
tmp/data/projects_flat/aaronw2_el_driver/version_current/working/working.kicad_pcb:
Copyright © 2020 Aaron Williams
tmp/data/projects_flat/aaronw2_flex_ears/version_current/working/working.kicad_pcb:
Flex Ear LEDs Copyright © 2019 by Aaron Williams
tmp/data/projects_flat/aaronw2_led_controller_gpio/version_current/working/working.kicad_pcb:
© 2020
